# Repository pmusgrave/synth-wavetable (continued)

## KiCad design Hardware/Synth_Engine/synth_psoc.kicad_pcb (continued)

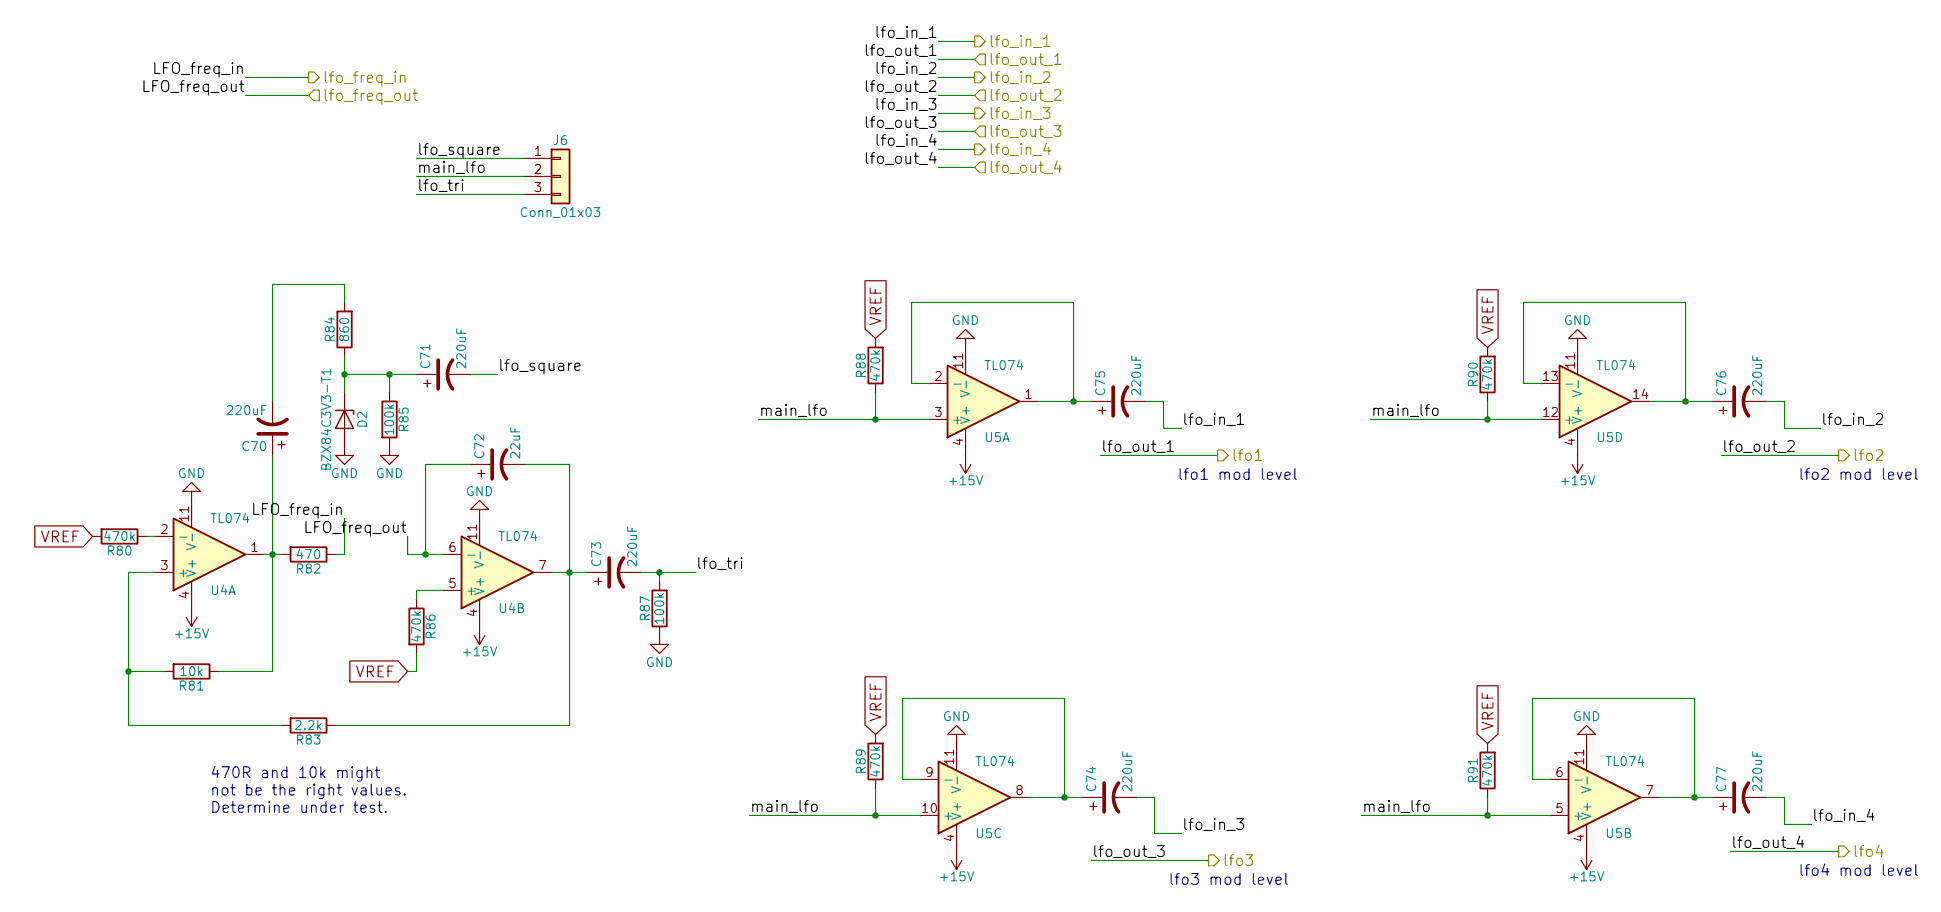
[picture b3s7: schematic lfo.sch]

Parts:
C70, C71, C73, C74, C75, C76, C77: 220uF; CP_Elec_8x10
C72: 22uF; CP_Elec_5x5.7
D2: BZX84C3V3-T1; SOT-23-3
J6: Conn_01x03; Pin_Header_Straight_1x03_Pitch2.54mm
R80, R86, R88, R89, R90, R91: 470k; 0805
R81: 10k; 0805
R82: 470; 0805
R83: 2.2k; 0805
R84: 860; 0805
R85, R87: 100k; 0805
U4, U5: TL074; SOIC-14_W3.9mm

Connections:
+15V: U4.4 (V+), U5.4 (V+); also elsewhere on the board
/LFO Modulation and Routing/lfo_square: C71.2, J6.1
/LFO Modulation and Routing/lfo_tri: C73.2, J6.3, R87.2
/LFO Modulation and Routing/main_lfo: J6.2, R88.1, R89.1, R90.1, R91.1, U5.3 (+), U5.5 (+), U5.10 (+), U5.12 (+)
/lfo_freq_in: R82.1; also elsewhere on the board
/lfo_freq_out: C72.1, U4.6 (-); also elsewhere on the board
/lfo_in_1: C75.2; also elsewhere on the board
/lfo_in_2: C76.2; also elsewhere on the board
/lfo_in_3: C74.2; also elsewhere on the board
/lfo_in_4: C77.2; also elsewhere on the board
GND: D2.2 (A), R85.2, R87.1, U4.11 (V-), U5.11 (V-); also elsewhere on the board
unnamed: C70.1, R81.1, R82.2, U4.1
unnamed: C70.2, R84.2
unnamed: C71.1, D2.1 (K), R84.1, R85.1
unnamed: C72.2, C73.1, R83.1, U4.7
unnamed: C74.1, U5.8, U5.9 (-)
unnamed: C75.1, U5.1, U5.2 (-)
unnamed: C76.1, U5.13 (-), U5.14
unnamed: C77.1, U5.6 (-), U5.7
unnamed: R80.1, U4.2 (-)
unnamed: R81.2, R83.2, U4.3 (+)
unnamed: R86.1, U4.5 (+)
VREF: R80.2, R86.2, R88.2, R89.2, R90.2, R91.2; also elsewhere on the board

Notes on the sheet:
470R and 10k might not be the right values. Determine under test.
lfo4 mod level
lfo2 mod level
lfo3 mod level
lfo1 mod level

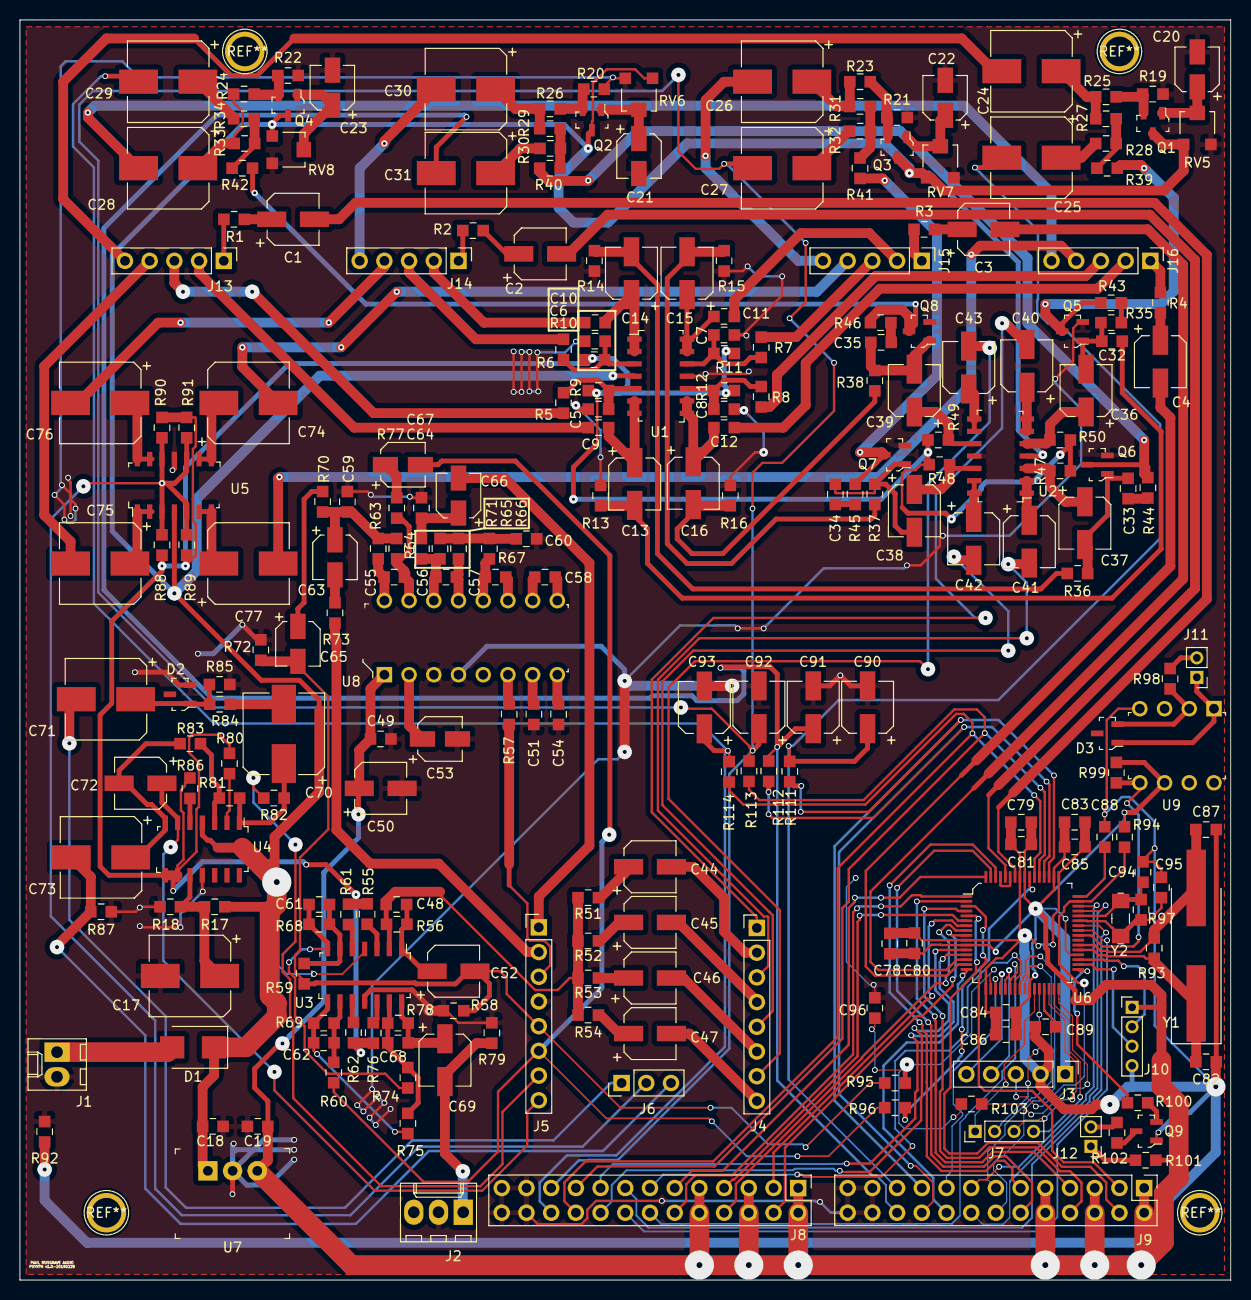
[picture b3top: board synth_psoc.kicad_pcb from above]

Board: 2 copper layers, 124.5 x 129.5 mm, 246 parts (0 on the bottom side), 211 nets.

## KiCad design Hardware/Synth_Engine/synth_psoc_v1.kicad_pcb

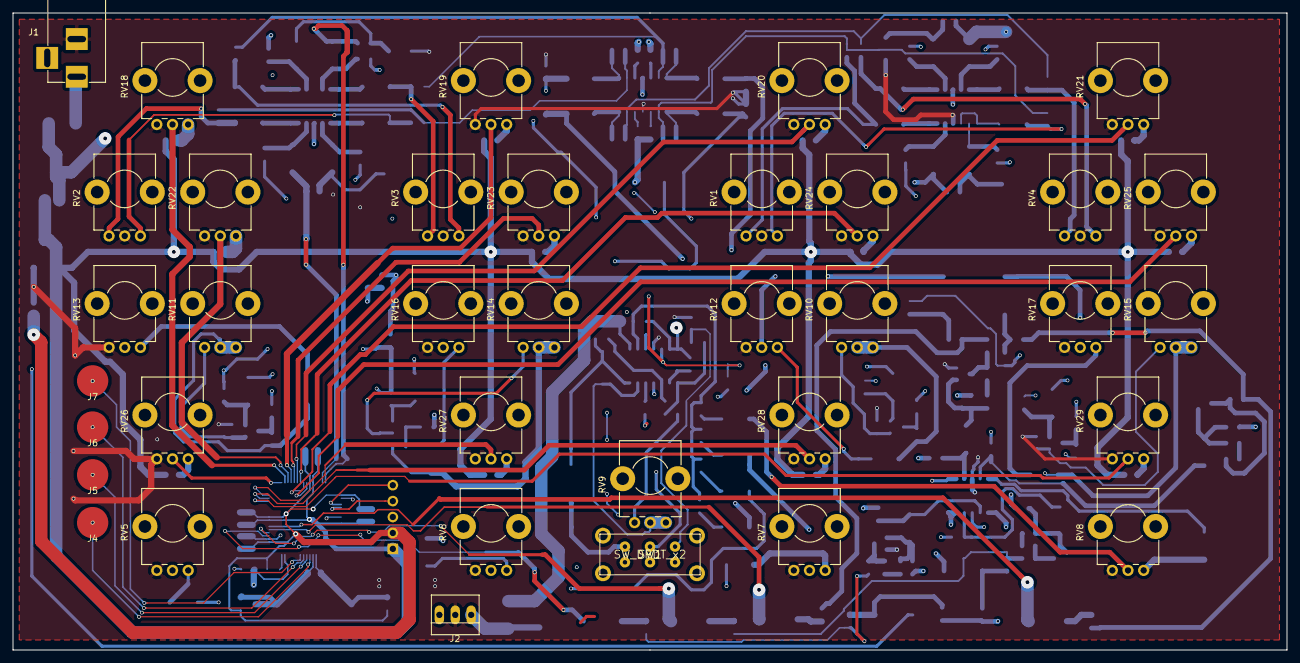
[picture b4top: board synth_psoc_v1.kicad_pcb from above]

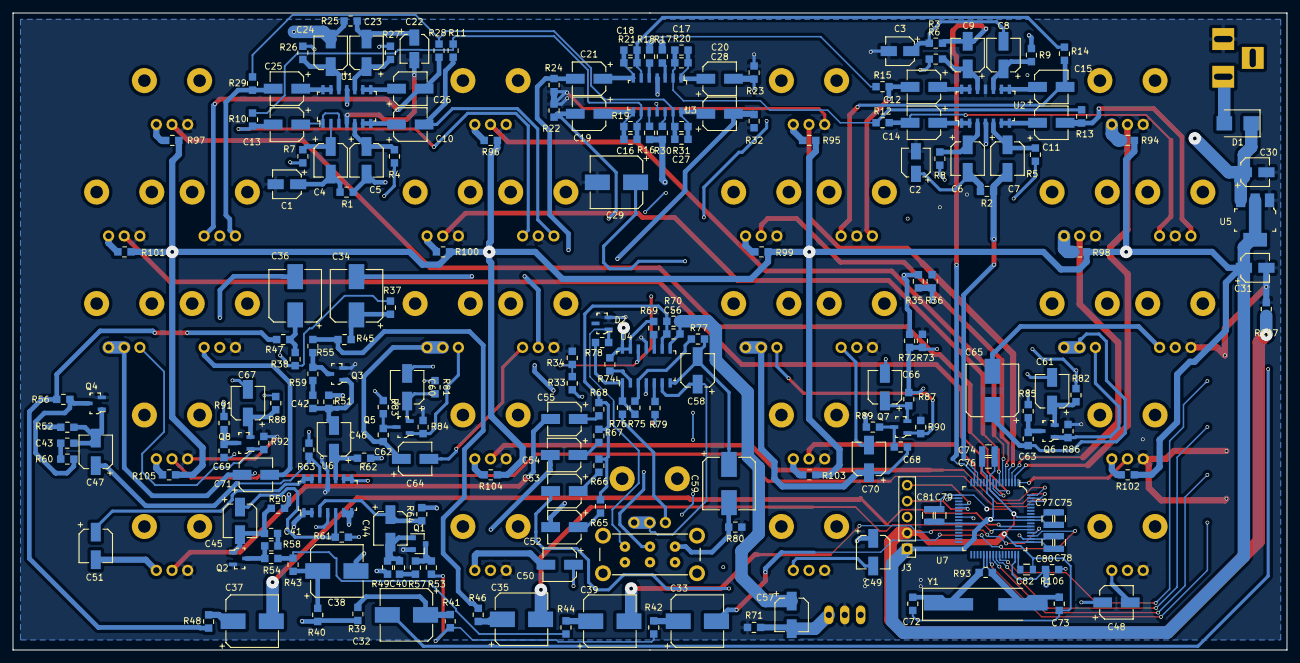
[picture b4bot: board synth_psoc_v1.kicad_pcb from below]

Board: 4 copper layers, 203.2 x 101.6 mm, 244 parts (208 on the bottom side), 177 nets.

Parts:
C1, C2, C3, C22, C30: 1uF; CP_Elec_4x4.5
C4, C5, C6, C7, C8, C9, C10, C11, C12, C13, C14, C15, C19, C20, C21, C23, C24, C25, C26, C28, C44, C45, C46, C47, C48, C49, C50, C51, C52, C53, C54, C55, C57, C58, C60, C61, C64, C66, C67, C70, C71: 22uF; CP_Elec_5x5.7
C16, C17, C18, C27: 100p; 0805
C29, C59, C65: 220uF; CP_Elec_8x10
C31: 4.7uF; CP_Elec_4x5.7
C32, C33, C34, C35, C36, C37, C38, C39: 220u; CP_Elec_8x10
C40, C41, C42, C43: 1nF; 0805
C56: 100pF; 0805
C62, C63, C68, C69: 33nF; 0805
C72, C73: 22pF; 0805
C74, C75, C78, C81, C82: 1uF; C_0805
C76, C77, C79, C80: 0.1uF; C_0805
D1: D_Schottky; D_SMB
D2: BZX84C3V3-T1; SOT-23-3
J1: Barrel_Jack; BARREL_JACK
J2: Audio-Jack-2_Switch; PINHEAD1-3
J3: SWD_programming; Pin_Header_Straight_1x05_Pitch2.54mm
J4: Capsense_0; Capsense_button
J5: Capsense_1; Capsense_button
J6: Capsense_2; Capsense_button
J7: Capsense_3; Capsense_button
Q1: MMBFJ177; SOT-23
Q2, Q3, Q4: MMBFJ177; SOT-23-3
Q5, Q6, Q7, Q8: 2N3904; SOT-23-3
R1, R2, R3, R25: 1k; 0805
R4, R5, R6, R7, R8, R9, R16, R17, R18, R26, R27, R30, R37, R38, R39, R40, R61, R62, R63, R64, R69, R74, R79, R81, R82, R87, R88: 470k; 0805
R10, R11, R12, R13, R14, R15, R19, R20, R21, R28, R29, R31, R65, R66, R67, R68, R70, R71, R72, R73, R75, R83, R84, R85, R86, R89, R90, R91, R92: 10k; 0805
R22, R23, R24, R32, R33, R34, R80: 100k; 0805
R35, R36, R49, R50, R51, R52: 22k; 0805
R41, R43, R45, R47, R53, R54, R55, R56, R57, R58, R59, R60, R93: 1MEG; 0805
R42, R44, R46, R48: 500k; 0805
R76: 470; 0805
R77: 2.2k; 0805
R78: 860; 0805
R94, R95, R96, R97, R98, R99, R100, R101, R102, R103, R104, R105, R106, R107: R; 0805
RV1, RV2, RV3, RV4: 100k-S; Potentiometer_Bourns_PTV09A-1_Horizontal
RV5, RV6, RV7, RV8: 100k; Potentiometer_Bourns_PTV09A-1_Horizontal
RV9, RV12, RV13, RV16, RV17: 10kA; Potentiometer_Bourns_PTV09A-1_Horizontal
RV10, RV11, RV14, RV15: 10kB; Potentiometer_Bourns_PTV09A-1_Horizontal
RV18, RV19, RV20, RV21, RV22, RV23, RV24, RV25: 20kA; Potentiometer_Bourns_PTV09A-1_Horizontal
RV26, RV27, RV28, RV29: 20kB; Potentiometer_Bourns_PTV09A-1_Horizontal
SW1: SW_DPDT_x2; SWITCHE-DPDT
U1, U2, U3, U4, U6: TL074; SOIC-14_W3.9mm
U5: LD1117S33CTR; SOT-223
U7: CY8C4246AZI-L445; LQFP-64_10x10mm
Y1: Crystal; Crystal_SMD_HC49-SD_HandSoldering

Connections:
+3V3: C31.1, C74.1, C75.1, C76.1, C77.1, C78.1, C79.1, C80.1, C81.1, J3.1, R94.1, R95.1, R96.1, R97.1, R98.1, R99.1, R100.1, R101.1, R102.1, R103.1, R104.1, R105.1, R106.1, U5.2, U5.4, U7.11, U7.26, U7.50, U7.56
+15V: C30.1, D1.1, R33.1, R35.2, R72.1, R83.1, R85.1, R89.1, R91.1, U1.11, U2.4, U3.4, U4.4, U5.3, U6.4
/Envelope/env_out_1: C52.2, RV5.2
/Envelope/env_out_2: C53.2, RV6.2
/Envelope/env_out_3: C54.2, RV7.2
/Envelope/env_out_4: C55.2, RV8.2
/Envelope/lfo1: C32.2, RV13.2
/Envelope/lfo2: C38.2, RV16.2
/Envelope/lfo3: C34.2, RV12.2
/Envelope/lfo4: C36.2, RV17.2
/Envelope/lfo_bias: R35.1, R36.2, R37.1, R38.1, R39.1, R40.1
/Filters/filter_out_1: C20.2, R23.1, R49.2
/Filters/filter_out_2: C21.2, R24.1, R50.2
/Filters/filter_out_3: C19.2, R22.1, R51.2
/Filters/filter_out_4: C28.2, R32.1, R52.2
/Filters/osc1: C7.2, R2.2, U7.14
/Filters/osc2: C9.2, R3.2, U7.15
/Filters/osc3: C5.2, R1.2, U7.18
/Filters/osc4: C24.2, R25.2, U7.24
/LFO Modulation and Routing/bias: R72.2, R73.1, R81.1, R82.1, R87.1, R88.1
/LFO Modulation and Routing/lfo_square: D2.1, R78.1, SW1.3
/LFO Modulation and Routing/lfo_tri: C59.2, R80.2, SW1.1
/LFO Modulation and Routing/main_lfo: C60.2, C61.2, C66.2, C67.2, SW1.2
/Microcontroller/SCLK: J3.4, U7.21
/Microcontroller/SDAT: J3.5, U7.20
/Microcontroller/XRES: J3.3, R106.2, U7.47
/Microcontroller/envelope_pwm_1: C33.2, U7.51
/Microcontroller/envelope_pwm_2: C39.2, U7.52
/Microcontroller/envelope_pwm_3: C35.2, U7.53
/Microcontroller/envelope_pwm_4: C37.2, U7.54
/Microcontroller/osc1_freq_wiper: RV18.2, U7.2
/Microcontroller/osc1_pwm_wiper: RV22.2, U7.3
/Microcontroller/osc1_speed: RV26.2, U7.1
/Microcontroller/osc2_freq_wiper: RV19.2, U7.4
/Microcontroller/osc2_pwm_wiper: RV23.2, U7.5
/Microcontroller/osc2_speed: RV27.2, U7.64
/Microcontroller/osc3_freq_wiper: RV20.2, U7.6
/Microcontroller/osc3_pwm_wiper: RV24.2, U7.7
/Microcontroller/osc3_speed: RV28.2, U7.63
/Microcontroller/osc4_freq_wiper: RV21.2, U7.8
/Microcontroller/osc4_pwm_wiper: RV25.2, U7.9
/Microcontroller/osc4_speed: RV29.2, U7.62
GND: C1.2, C2.2, C3.2, C22.2, C29.2, C30.2, C31.2, D2.2, J1.2, J2.2, Q1.2, Q2.2, Q3.2, Q4.2, R22.2, R23.2, R24.2, R32.2, R34.2, R36.1, R71.1, R73.2, R80.1, R84.2, R86.2, R90.2, R92.2, R107.1, RV1.2, RV2.2, RV3.2, RV4.2, RV5.3, RV6.3, RV7.3, RV8.3, RV12.3, RV13.3, RV16.3, RV17.3, RV18.3, RV19.3, RV20.3, RV21.3, RV22.3, RV23.3, RV24.3, RV25.3, RV26.3, RV27.3, RV28.3, RV29.3, U1.4, U2.11, U3.11, U4.11, U5.1, U6.11
GNDD: C72.2, C73.2, C74.2, C75.2, C76.2, C77.2, C78.2, C79.2, C80.2, C81.2, C82.2, J3.2, R107.2, U7.10, U7.17, U7.49, U7.57
unnamed: C1.1, C4.2, R1.1
unnamed: C2.1, C6.2, R2.1
unnamed: C3.1, C8.2, R3.1
unnamed: C4.1, R7.2, U1.2
unnamed: C5.1, R4.2, U1.5
unnamed: C6.1, R8.2, U2.3
unnamed: C7.1, R5.2, U2.5
unnamed: C8.1, R9.2, U2.10
unnamed: C9.1, R6.2, U2.12
unnamed: C10.1, U1.6, U1.7
unnamed: C10.2, R11.2, RV1.3
unnamed: C11.1, U2.6, U2.7
unnamed: C11.2, R13.2, RV2.3
unnamed: C12.1, U2.13, U2.14
unnamed: C12.2, R15.2, RV3.3
unnamed: C13.1, U1.1, U1.3
unnamed: C13.2, R10.2, RV1.1
unnamed: C14.1, U2.1, U2.2
unnamed: C14.2, R12.2, RV2.1
unnamed: C15.1, U2.8, U2.9
unnamed: C15.2, R14.2, RV3.1
unnamed: C16.1, C19.1, R19.1, U3.8
unnamed: C16.2, R10.1, R11.1, R19.2, U3.9
unnamed: C17.1, C20.1, R20.1, U3.1
unnamed: C17.2, R12.1, R13.1, R20.2, U3.2
unnamed: C18.1, C21.1, R21.1, U3.7
unnamed: C18.2, R14.1, R15.1, R21.2, U3.6
unnamed: C22.1, C23.2, R25.1
unnamed: C23.1, R27.2, U1.10
unnamed: C24.1, R26.2, U1.12
unnamed: C25.1, U1.13, U1.14
unnamed: C25.2, R29.2, RV4.3
unnamed: C26.1, U1.8, U1.9
unnamed: C26.2, R28.2, RV4.1
unnamed: C27.1, C28.1, R31.1, U3.14
unnamed: C27.2, R28.1, R29.1, R31.2, U3.13
unnamed: C29.1, R33.2, R34.1, U4.12
unnamed: C32.1, R39.2, R41.2
unnamed: C33.1, R42.2
unnamed: C34.1, R37.2, R45.2
unnamed: C35.1, R46.2
unnamed: C36.1, R38.2, R47.2
unnamed: C37.1, R48.2
unnamed: C38.1, R40.2, R43.2
unnamed: C39.1, R44.2
unnamed: C40.1, R57.2
unnamed: C40.2, C44.2, Q1.1, R49.1
unnamed: C41.1, R58.2
unnamed: C41.2, C45.2, Q2.1, R50.1
unnamed: C42.1, R59.2
unnamed: C42.2, C46.2, Q3.1, R51.1
unnamed: C43.1, R60.2
unnamed: C43.2, C47.2, Q4.1, R52.1
unnamed: C44.1, R64.1, U6.3
unnamed: C45.1, R61.1, U6.5
unnamed: C46.1, R62.1, U6.10
unnamed: C47.1, R63.1, U6.12
unnamed: C48.1, U6.1, U6.2
unnamed: C48.2, RV5.1
unnamed: C49.1, U6.6, U6.7
unnamed: C49.2, RV6.1
unnamed: C50.1, U6.8, U6.9
unnamed: C50.2, RV7.1
unnamed: C51.1, U6.13, U6.14
unnamed: C51.2, RV8.1
unnamed: C52.1, R65.2
unnamed: C53.1, R66.2
unnamed: C54.1, R67.2
unnamed: C55.1, R68.2
unnamed: C56.1, C57.1, R70.1, U4.8
unnamed: C56.2, R65.1, R66.1, R67.1, R68.1, R70.2, U4.9
unnamed: C57.2, J2.1, R71.2
unnamed: C58.1, RV9.1, RV9.2, U4.6
unnamed: C58.2, C59.1, R77.1, U4.7
unnamed: C60.1, Q5.2, R81.2
unnamed: C61.1, Q6.2, R82.2
unnamed: C62.1, Q5.3, R83.2
unnamed: C62.2, C64.1, RV10.1, RV10.2
unnamed: C63.1, Q6.3, R85.2
unnamed: C63.2, C65.1, RV11.1, RV11.2
unnamed: C64.2, RV12.1
unnamed: C65.2, RV13.1
unnamed: C66.1, Q7.2, R87.2
unnamed: C67.1, Q8.2, R88.2
unnamed: C68.1, Q7.3, R89.2
unnamed: C68.2, C70.1, RV14.1, RV14.2
unnamed: C69.1, Q8.3, R91.2
unnamed: C69.2, C71.1, RV15.1, RV15.2
unnamed: C70.2, RV16.1
unnamed: C71.2, RV17.1
unnamed: C72.1, R93.2, U7.37, Y1.1
unnamed: C73.1, R93.1, U7.38, Y1.2
unnamed: C82.1, U7.48
unnamed: D1.2, J1.1
unnamed: J4.1, U7.39
unnamed: J5.1, U7.40
unnamed: J6.1, U7.41
unnamed: J7.1, U7.42
unnamed: Q1.3, R53.1, R57.1
unnamed: Q2.3, R54.1, R58.1
unnamed: Q3.3, R55.1, R59.1
unnamed: Q4.3, R56.1, R60.1
unnamed: Q5.1, R84.1, RV10.3
unnamed: Q6.1, R86.1, RV11.3
unnamed: Q7.1, R90.1, RV14.3
unnamed: Q8.1, R92.1, RV15.3
unnamed: R16.1, U3.10
unnamed: R17.1, U3.3
unnamed: R18.1, U3.5
unnamed: R30.1, U3.12
unnamed: R41.1, R42.1, R53.2
unnamed: R43.1, R44.1, R54.2
unnamed: R45.1, R46.1, R55.2
unnamed: R47.1, R48.1, R56.2
unnamed: R69.1, U4.10
unnamed: R74.1, U4.2
unnamed: R75.1, R76.2, R78.2, U4.1
unnamed: R75.2, R77.2, U4.3
unnamed: R76.1, RV9.3
unnamed: R79.1, U4.5
unnamed: R94.2, RV18.1
unnamed: R95.2, RV19.1
unnamed: R96.2, RV20.1
unnamed: R97.2, RV21.1
unnamed: R98.2, RV22.1
unnamed: R99.2, RV23.1
unnamed: R100.2, RV24.1
unnamed: R101.2, RV25.1
unnamed: R102.2, RV26.1
unnamed: R103.2, RV27.1
unnamed: R104.2, RV28.1
unnamed: R105.2, RV29.1
VREF: R4.1, R5.1, R6.1, R7.1, R8.1, R9.1, R16.2, R17.2, R18.2, R26.1, R27.1, R30.2, R61.2, R62.2, R63.2, R64.2, R69.2, R74.2, R79.2, U4.13, U4.14

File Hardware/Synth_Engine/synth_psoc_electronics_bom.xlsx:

Reference | Quantity | Value | Footprint | Datasheet | Digi-Key_PN | MPN | Category | Family | DK_Datasheet_Link | DK_Detail_Page | Description | Manufacturer | Status
C16 C17 C18 C27 | 4 | 100p | digikey-footprints:0805
C1 C2 C22 C3 C30 | 5 | 1uF | Capacitors_SMD:CP_Elec_4x4.5
C29 C59 C65 | 3 | 220uF | Capacitors_SMD:CP_Elec_8x10
C31 | 1 | 4.7uF | Capacitors_SMD:CP_Elec_4x5.7
C32 C33 C34 C35 C36 C37 C38 C39 | 8 | 220u | Capacitors_SMD:CP_Elec_8x10
C40 C41 C42 C43 | 4 | 1nF | digikey-footprints:0805
C56 | 1 | 100pF | digikey-footprints:0805
C10 C11 C12 C13 C14 C15 C19 C20 C21 C23 C24 C25 C26 C28 C4 C44 C45 C46 C47 C48 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 | 41 | 22uF | Capacitors_SMD:CP_Elec_5x5.7
C62 C63 C68 C69 | 4 | 33nF | digikey-footprints:0805
C72 C73 | 2 | 22pF | digikey-footprints:0805
C74 C75 C78 C81 C82 | 5 | 1uF | Capacitors_SMD:C_0805
C76 C77 C79 C80 | 4 | 0.1uF | Capacitors_SMD:C_0805
D1 | 1 | D_Schottky | Diodes_SMD:D_SMB
D2 | 1 | BZX84C3V3-T1 | digikey-footprints:SOT-23-3
J1 | 1 | Barrel_Jack | Connectors:BARREL_JACK
J2 | 1 | Audio-Jack-2_Switch | Connectors:PINHEAD1-3
J3 | 1 | SWD_programming | Pin_Headers:Pin_Header_Straight_1x05_Pitch2.54mm
J4 | 1 | Capsense_0 | Cypress_capsense:Capsense_button
J5 | 1 | Capsense_1 | Cypress_capsense:Capsense_button
J6 | 1 | Capsense_2 | Cypress_capsense:Capsense_button
J7 | 1 | Capsense_3 | Cypress_capsense:Capsense_button
Q1 Q2 Q3 Q4 | 4 | MMBFJ177 | digikey-footprints:SOT-23-3
Q5 Q6 Q7 Q8 | 4 | 2N3904 | digikey-footprints:SOT-23-3
R10 R11 R12 R13 R14 R15 R19 R20 R21 R28 R29 R31 R65 R66 R67 R68 R70 R71 R72 R73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 | 29 | 10k | digikey-footprints:0805
R1 R2 R25 R3 | 4 | 1k | digikey-footprints:0805
R22 R23 R24 R32 R33 R34 R80 | 7 | 100k | digikey-footprints:0805
R42 R44 R46 R48 | 4 | 500k | digikey-footprints:0805
R35 R36 R49 R50 R51 R52 | 6 | 22k | digikey-footprints:0805
R41 R43 R45 R47 R53 R54 R55 R56 R57 R58 R59 R60 R93 | 13 | 1MEG | digikey-footprints:0805
R76 | 1 | 470 | digikey-footprints:0805
R77 | 1 | 2.2k | digikey-footprints:0805
R78 | 1 | 860 | digikey-footprints:0805
R16 R17 R18 R26 R27 R30 R37 R38 R39 R4 R40 R5 R6 R61 R62 R63 R64 R69 R7 R74 R79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 | 27 | 470k | digikey-footprints:0805
R100 R101 R102 R103 R104 R105 R106 R107 R94 R95 R96 R97 R98 R99 | 14 | R | digikey-footprints:0805
RV10 RV11 RV14 RV15 | 4 | 10kB | Potentiometers:Potentiometer_Bourns_PTV09A-1_Horizontal
RV12 RV13 RV16 RV17 RV9 | 5 | 10kA | Potentiometers:Potentiometer_Bourns_PTV09A-1_Horizontal
RV18 RV19 RV20 RV21 RV22 RV23 RV24 RV25 | 8 | 20kA | Potentiometers:Potentiometer_Bourns_PTV09A-1_Horizontal
RV1 RV2 RV3 RV4 | 4 | 100k-S | Potentiometers:Potentiometer_Bourns_PTV09A-1_Horizontal
RV26 RV27 RV28 RV29 | 4 | 20kB | Potentiometers:Potentiometer_Bourns_PTV09A-1_Horizontal
RV5 RV6 RV7 RV8 | 4 | 100k | Potentiometers:Potentiometer_Bourns_PTV09A-1_Horizontal
SW1 | 1 | SW_DPDT_x2 | SparkFun-Electromechanical:SWITCHE-DPDT
U1 U2 U3 U4 U6 | 5 | TL074 | digikey-footprints:SOIC-14_W3.9mm
U5 | 1 | LD1117S33CTR | digikey-footprints:SOT-223 | http://www.st.com/content/ccc/resource/technical/document/da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 | 497-1241-1-ND | LD1117S33CTR | Integrated Circuits (ICs) | PMIC - Voltage Regulators - Linear | http://www.st.com/content/ccc/resource/technical/document/da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 | /product-detail/en/stmicroelectronics/LD1117S33CTR/497-1241-1-ND/586241 | IC REG LINEAR 3.3V 800MA SOT223 | STMicroelectronics | Active
U7 | 1 | CY8C4246AZI-L445 | digikey-footprints:LQFP-64_10x10mm
Y1 | 1 | Crystal | Crystals:Crystal_SMD_HC49-SD_HandSoldering

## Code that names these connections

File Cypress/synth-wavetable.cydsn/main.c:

#include <project.h>
#include "AudioControl.h"
#include "Interrupts.h"
#include "AudioOut.h"
#include "globals.h"
#include "midi.h"
#include "spi_master.h"

/*******************************************************************************
* main
*******************************************************************************/
int main() {
    LED_Write(1);
    isr_trigger_StartEx(envelope_trigger_interrupt);
    
    CC_Timer_Start();
    isr_MIDI_CC_TimerDone_StartEx(MIDI_CC_TimerDone);

    uint16_t attack = 0;
    uint16_t decay = 0;
    uint16_t sustain = 0;
    uint16_t release = 0;
    uint16_t waveshape = 0;
    ADC_Start();
    ADC_StartConvert();
    isr_ADC_EOC_StartEx(ADC_EOC);
    
    UART_Start();
    SpiInit();
    
    // Init USB and MIDI
    // references Cypress USB MIDI code example
    USB_Start(DEVICE, USB_DWR_VDDD_OPERATION); 
    MIDI1_UART_Start();
    //MIDI_RX_StartEx(MIDI_RX_VECT);
    //UART_UartPutString("USB MIDI initialized...\r\n");
    
    for(uint32_t i = 0; i < 10000; i++){
        CyGlobalIntDisable;
        ProcessUSBMIDI();
        CyGlobalIntEnable;
        CyDelayUs(100);
    }
    
    CyGlobalIntEnable;
    
    SPI_RxDMA_Start((void *)SPI_RX_FIFO_RD_PTR, (void *)masterRxBuffer);
    SPI_TxDMA_Start((void *)masterTxBuffer, (void *)SPI_TX_FIFO_WR_PTR);
    
    struct midi_msg test0 = {USB_MIDI_NOTE_ON, 42, 127, 0};
    struct midi_msg test1 = {USB_MIDI_NOTE_OFF, 42, 127, 0};
    struct midi_msg test2 = {USB_MIDI_NOTE_ON, 43, 127, 0};
    struct midi_msg test3 = {USB_MIDI_NOTE_OFF, 43, 127, 0};
    struct midi_msg test4 = {USB_MIDI_NOTE_ON, 44, 127, 0};
    struct midi_msg test5 = {USB_MIDI_NOTE_OFF, 44, 127, 0};

    uint8_t init_msg[14] = {"Hello world!\n"};
    for(int i = 0; i < 14; i++){
        //ProcessSpiTx(init_msg[i]);   
        UART_UartPutChar(init_msg[i]);
    }
    
    for(;;) {
        ProcessUSBMIDI();
        
        if(trigger_flag) {
            if((midi_msg_queue.head != midi_msg_queue.tail)){// && (CTS_Read() == 0)){
                struct midi_msg current_msg = dequeue();
                UART_UartPutChar(current_msg.byte0);
                UART_UartPutChar(current_msg.byte1);
                UART_UartPutChar(current_msg.byte2);
                UART_UartPutChar(' ');
                //ProcessSpiTx(current_msg.byte0);
                //ProcessSpiTx(current_msg.byte1);
                //ProcessSpiTx(current_msg.byte2);
                //ProcessSpiTx(' ');
            }
            else {
                UART_UartPutChar('\n');
                //ProcessSpiTx('\n');
                for(int i = 0; i < 14; i++){
                    //UART_UartPutChar(init_msg[i]);
                    //ProcessSpiTx(init_msg[i]);   
                }
            }
        }
        else{
            for(int i = 0; i < 15; i++){
                UART_UartPutChar(init_msg[i]);
                //ProcessSpiTx(init_msg[i]);
                CyDelay(2);
            }
            
            if((midi_msg_queue.head != midi_msg_queue.tail)){// && (CTS_Read() == 0)){
                struct midi_msg current_msg = dequeue();
                UART_UartPutChar(current_msg.byte0);
                UART_UartPutChar(current_msg.byte1);
                UART_UartPutChar(current_msg.byte2);
                //ProcessSpiTx(current_msg.byte0);
                //ProcessSpiTx(current_msg.byte1);
                //ProcessSpiTx(current_msg.byte2);
            }
            else {
                UART_UartPutChar('\n');
                //ProcessSpiTx('\n');
                enqueue(test0);
                enqueue(test1);
                enqueue(test2);
                enqueue(test3);
                enqueue(test4);
                enqueue(test5);
            }
        }
        
        if(update_ADC_flag){
            attack = ADC_GetResult16(0);
            decay = ADC_GetResult16(1);
            sustain = ADC_GetResult16(2);
            release = ADC_GetResult16(3);
            waveshape = ADC_GetResult16(4);
            
            update_ADC_flag = 0;
        }
        
        if(MIDI_CC_update_flag) {
            MIDI_CC_update_flag = 0;
            
            struct midi_msg attack_cc = {
                0x14,
                (uint8_t)(attack>>4),
                0,
                0
            };
            
            struct midi_msg decay_cc = {
                0x15,
                (uint8_t)(decay>>4),
                0,
                0
            };
            
            struct midi_msg sustain_cc = {
                0x16,
                (uint8_t)(sustain>>4),
                0,
                0
            };
            
            struct midi_msg release_cc = {
                0x17,
                (uint8_t)(release>>4),
                0,
                0
            };
            struct midi_msg waveshape_cc = {
                0x17,
                (uint8_t)(waveshape>>4),
                0,
                0
            };
            
            enqueue(attack_cc);
            enqueue(decay_cc);
            enqueue(sustain_cc);
            enqueue(release_cc);
            enqueue(waveshape_cc);
            
            Green_LED_Write(~Green_LED_Read());
        }
    }
}

/* [] END OF FILE */

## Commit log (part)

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2019-09-19 start configuring audio path * add UART debug strings * fix codec initialization * remove dynamically allocated memory for now due to bugs * decrease number of samples per wave to a 100 Hz rate
2019-09-19 clean sine wave output via DAC
2019-09-19 test square wave and fix issue with incorrect buffer index
2019-09-21 cleanest sine wave so far. * Fix a lot of DMA triggering. * Double buffer the I2S data. * Increase buffer size by factor of 10. * Disable interrupts while writing to initial buffer.
2019-09-22 fix bug in generating ramp waveshapes
2019-09-23 basic 2-voice polyphony. Has some timing issues.
2019-09-24 use phase-accumulator DDS technique to allow fractional frequencies
2019-09-24 clean up unused code from Cypress examples. also add polyphony again with new method. Still haven't fixed timing issues. It's spending all its time doing math to fill the buffer and doesn't have enou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
2019-09-25 implement ping-pong double buffering. did not fix buffer timing issues
2019-09-25 tested and confirmed double buffering behavior but there is still a bug sending the correct samples to the DAC. It's no longer clicking due to buffer size, now it's a phase offset when the buffers ch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
2019-09-25 change from multiplexed DMA triggers to single DMA component with chained descriptors. * significantly improved, but not perfect. * clean sine wave about half the time, clicking noise about half the 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
2019-09-26 use 512 sample size for buffers. Cleanest sine wave so far.
2019-09-26 significantly cleaner polyphony * two voices for now
2019-09-26 pushing limits of polyphony. Adding voices works fine, but when I scale values to prevent distortion, I run into buffer timing issues because it's too much math to do. I believe the buffer size is as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
2019-09-26 can handle 4 voice polyphony without buffer underrun. This only works when divisions are by powers of 2 (e.g. /8) because this compiles down to a bit shift and is fast enough. This is effectively the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
2019-09-26 can handle 8 voice polyphony by scaling the base wave amplitude. Dividing by the number of voices prevents the need to divide in the buffer processing function. This does reduce SNR, though.
2019-09-26 first pass LFO some (but minimal) buffer underruns even with only one voice
2019-09-26 leave this branch configured for polyphony remove LFO changes on this branch and work on those in some other branch
2019-09-26 fix clicking sound when LFO reaches end of period
2019-09-26 lfo pitch modulation
2019-09-27 pushbutton triggers and ramps up in attack mode
2019-09-27 first pass ADSR completed. Timing range is not right, but ramp logic is all in place.
2019-09-27 add USB MIDI components print debug string to UART when midi notes messages are received
2019-09-28 polyphony working with MIDI. Disable envelope attack/release while debugging.
2019-09-28 8 voice polyphony some sporadic buffer underruns with this many voices. Had to do some nonsense to get USB MIDI to succeed now.
2019-10-01 add SPI component in master mode * :change DMA descriptor to transfer between SPI Rx FIFO and I2S Tx FIFO
2019-10-08 bit bang serial communication from FPGA
2019-10-09 clean up DMA transfer code. Still having an issue with RAM to I2S FIFO DMA not triggering.
2019-10-09 successfully pass data through entire audio path. * Use chained DMA transfers with 2 buffers. * This confirms SPI->RAM->I2S codec audio path is configured correctly. * DO NOT change PSoC SPI configur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
2019-10-10 move Cypress code into new directory to keep things separate
2019-10-10 generate STM32 HAL code with CubeMX with SPI in full duplex slave mode.
2019-10-11 successfully send data out of SPI. Data format/index are not correct, but this confirms the peripheral is configured correctly and sending out at least something.
2019-10-11 send one sample at a time
2019-10-11 closest thing to a sinewave using SPI so far
2019-10-16 move FPGA DDS files into this project directory * MIDI control of single notes is working * ADSR is functional
2019-10-16 add other waveshapes to FPGA
2019-10-17 significantly clean up verilog code. * split register definitions near blocks where they are used * simplify SPI command switches and byte counting * change from less than/equal to byte counter to st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
2019-10-17 verify 16-bit values are being stored correctly in FPGA * needed to increment byte counter outside of all case statements and adjust how mosi_data_16bit was being updated
2019-10-17 confirmed 2-voice polyphony, no envelopes
2019-10-17 confirmed envelope working for one voice
2019-10-17 confirmed 2 voice polyphony with envlopes
2019-10-19 improve receiving SPI commands and byte counting and change SPI commands to MIDI note messages
2019-10-19 implement envelope multiplier on FPGA side
2019-10-19 sine wave with ramp envelope
2019-10-19 fix note on/off logic
2019-10-19 remove unnecessary if(note_on) conditional
2019-10-20 change phase and output value to arrays, but having (presumably) timing issues when I try to increase the number of elements to anything greater than 8.
2019-10-21 polyphony (!)
2019-10-23 indicate voices active with leds
2019-10-24 further reduce MIDI note error rate. The only detectable issue right now is sometimes note off messages are missed and the note stays on.
2019-10-24 block until SPI DMA is complete
2019-10-24 attack envelope on FPGA
2019-10-25 implement most of ADSR on FPGA. Release has some problems due to how note assignment currently works. Note assignment is not final though, so this can wait.
2019-10-26 floating point conversion and addition complete
2019-10-26 8 voice polyphony using floating point addition. Still not ideal because I end up dividing by 8 anyway, which removes the precision gained by using FP math with fewer than 8 voices active.
2019-10-26 divide by number of voices currently active. The result is not as good as I was hoping. It works, but there is noticeable volume drop when you add voices.
2019-10-27 change to Makefile generated code from STM32CubeMX. * Verify SPI reception is working * Add SPI slave select condition
2019-10-27 add MIDI Rx code currently untested
2019-10-28 working on MIDI note messages. * verify that setting a value in note_on array produces sinewave output. * MIDI messages via SPI not fully functioning yet.
2019-10-28 trigger a sinewave with a MIDI note on message via SPI
2019-10-30 add timer to more closely control sample rate * also clean things up a bit: * move phase accumulator update code into function * move R2R DAC update code into function
2019-10-30 clean up main DDS generator * fix output frequency precision: * only update output values based in timer ISR * this allows more control over the output frequency because it updates at a known rate. *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
2019-10-30 separate envelopes from output values
2019-10-30 create envelope state machine
2019-11-06 use internal DAC instead of R2R not using DMA yet
2019-11-07 settle on 16 voice maximum with 48kHz sample rate. Also sum 2 waveforms per voice
2019-11-07 improve ADSR * add timer to trigger notes periodically (for testing) * improve ADSR ranges * doing this required modifying the DDS_SCALE_FACTOR constant which means the MIDI note table will have to b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
2019-11-08 implement LFOs
2019-11-08 fix MIDI * change CPOL from low to high * improve MIDI note message state machine in main loop
2019-11-08 change PSoC code to simply pass all MIDI messages through SPI link rather than dispatching to notes and checking note_on status
2019-11-09 add MIDI note message queue hopefully to avoid losing MIDI messages. Currently untested.
2019-11-09 fix SPI DMA transfer size also change SPI polarity settings. Verified with UART that MIDI queue is sending out values as expected.
2019-11-12 add pushbutton switch to make device send constant MIDI messages. Press switch to toggle between constant messages or MIDI messages from USB queue.
2019-11-12 fid MIDI bugs * read one SPI byte at a time * scan for NOTE ON/OFF messages * set flags to read following bytes
2019-11-12 add control change messages with ADSR values * change struct from midi_note_msg to more general midi_msg * create CC midi messages with ADC readings * enqueue CC midi messages along with note messages
2019-11-12 receive ADSR CC messages * currently untested because the PSoC is flooding the MIDI msg queue with ADSR values, which is causing note messages to be missed
2019-11-13 fix NOTE/CC issue from previous commit
2019-11-13 change from MIDI message queue to byte queue on Rx side. This makes more sense now that Tx is sending one byte at a time.
2019-11-13 move debug UART code into functions to clean things up
2019-11-13 remove FPGA code from STM branch
2019-11-15 refactor USB midi code
2019-11-15 refactor main Cypress code. * clean things up considerably * remove dead UART, Codec, I2S code * move SPI code into separate files
2019-11-15 refactor STM32 code * move SPI, envelopes, global variables into separate files * fix basic SPI transactions with 1-byte-at-a-time blocking function calls
2019-11-16 set ADSR values in refactored version * still having some SPI bugs, but I think I can avoid them for now. * Whenever any ADSR pot value reaches 0x44, SPI loses synchronization * Refactor SPI code to 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
2019-11-18 change from SPI to UART on PSoC
2019-11-18 reduce baud rate to 9600
2019-11-18 switch from SPI to UART Rx on STM32
2019-11-18 add sch and pcb layout files from v1 board. Basically, I just need to copy the microcontroller part and ditch the rest, but it'll save time to do that much.
2019-11-19 add waveshape ADC and CC MIDI message
2019-11-19 add STM32F429 to schematic and rename to current project name
2019-11-19 restart Cypress schematic * I was running into some KiCAD library issues between Windows and Linux * So, just starting over from scratch on linux. * Add CY8C4246 to schematic * Add MIDI hardware to s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
2019-11-19 add power regulation to schematic
2019-11-19 add SSI2144 implementation * basically default datasheet version
2019-11-19 fix some ground/VREF mixups on filter schematic
2019-11-19 add 3.3V voltage regulator
2019-11-19 add SWD debugging/programming header to STM32 schematic
2019-11-19 add (optional) external crystal to STM32 schematic. I don't know if an external crystal is necessary or not but it's good to have pads for it on the board if I need it. As I understand it, timing cri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
2019-11-21 add 3.3V analog regulator and add power nets to AK4490
2019-11-21 add filter potentiometers I believe filter is finalized now.
2019-11-21 add I/O connections between DAC and STM32 pages
2019-11-21 add pullup resistors to I2C lines
2019-11-21 add missing ground connections to AK4490 Probably need to double check all the grounding on this again.
2019-11-21 add filtering in front of 3.3V regulators
2019-11-21 clean up USB connector No need to connect this to anything other than PSoC
2019-11-21 regenerate STM code for new IC version This overwrote all my code though, so I still have to pull that in from another branch
2019-11-21 add in application code to custom hardware version builds successfully
2019-11-21 change PSoC firmware to use new IC. builds successfully.
2019-11-21 add I2S, I2C, UART, DAC config pins to STM32
2019-11-22 assign footprints to schematic symbols.
2019-11-22 initialize PCB layout files, generate netlist
2019-11-25 route 3.3VD voltage regulator and control MCU
2019-11-25 route STM32 bypass caps and programming header
2019-11-26 add separate PCB with potentiometers and switches and connector between control board and synth engine
2019-11-27 initial routing complete. Still need to do ground plane pours. There are still some issues with incorrect footprints.
2019-11-27 add ground plane copper pours
2019-12-03 fix some footprint errors
2019-12-03 PCBv1 as built. generate BOM and gerbers
2019-12-14 add pdf schematic
2019-12-19 port DAC code from previous project to STM32. No audio out yet, but I've verified STM32 is sending both I2C and I2S data
